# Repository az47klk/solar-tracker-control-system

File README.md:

# Solar-Tracker: Güneş Paneli Güç Takip ve Kontrol Sistemi

Bu proje, hareketli güneş paneli sistemlerinin güvenli şekilde çalışmaları için, anlık güç takibi yapmak ve çevresel verileri (sıcaklık, zaman vb.) yönetmek amacıyla geliştirilmiş bir gömülü kontrol sistemidir. Proje; donanım tasarımı (PCB), düşük seviyeli sürücü yazılımı ve endüstriyel haberleşme protokollerini kapsamaktadır.

## Teknik Özellikler
Sistem, endüstriyel standart gereksinimleri dikkate alınarak tasarlanmıştır:

* **Kontrol Birimi:** STM32 Mikrodenetleyici tabanlı mimari 
* **Haberleşme:** * **RS485 (Modbus):** Uzak mesafe veri iletimi ve endüstriyel cihaz entegrasyonu.
    * **I2C & UART:** Sensör ve çevre birimleri ile iletişim.
* **Donanım Bileşenleri:**
    * **MAX485:** Diferansiyel sinyal işleme ve gürültü bağışıklığı.
    * **DS1307 RTC:** Gerçek zamanlı saat takibi ile zaman bazlı hareket senaryoları.
    * **JW2 Röle Kontrolü:** Panel hareket mekanizması için güç yönetimi.
    * **128x64 OLED:** Yerel kullanıcı arayüzü ve anlık veri izleme.
* **PCB Tasarımı:** **KiCad** kullanılarak hazırlanan, sinyal bütünlüğü ve güç dağıtımı optimize edilmiş özgün devre kartı.

## Donanım Mimarisi
Proje kapsamında geliştirilen güç takip kartı şu işlevleri yerine getirmektedir:
1.  **Veri Toplama:** Sıcaklık sensörlerinden gelen verilerin işlenmesi.
2.  **Güç Yönetimi:** Röle katmanı üzerinden motor sürücülerin kontrol edilmesi.
3.  **HMI Entegrasyonu:** Sistem durumunun (gerilim, akım, zaman, sıcaklık) OLED ekran üzerinde gösterilmesi.
4.  **Haberleşme Katmanı:** Toplanan verilerin RS485 üzerinden merkezi bir birime aktarılması.

## Dosya Yapısı
* `/Hardware`: KiCad şema ve PCB tasarım dosyaları (Gerber dahil).
* `/Software`: C++ ile geliştirilen kontrol yazılımı ve sürücü kütüphaneleri.

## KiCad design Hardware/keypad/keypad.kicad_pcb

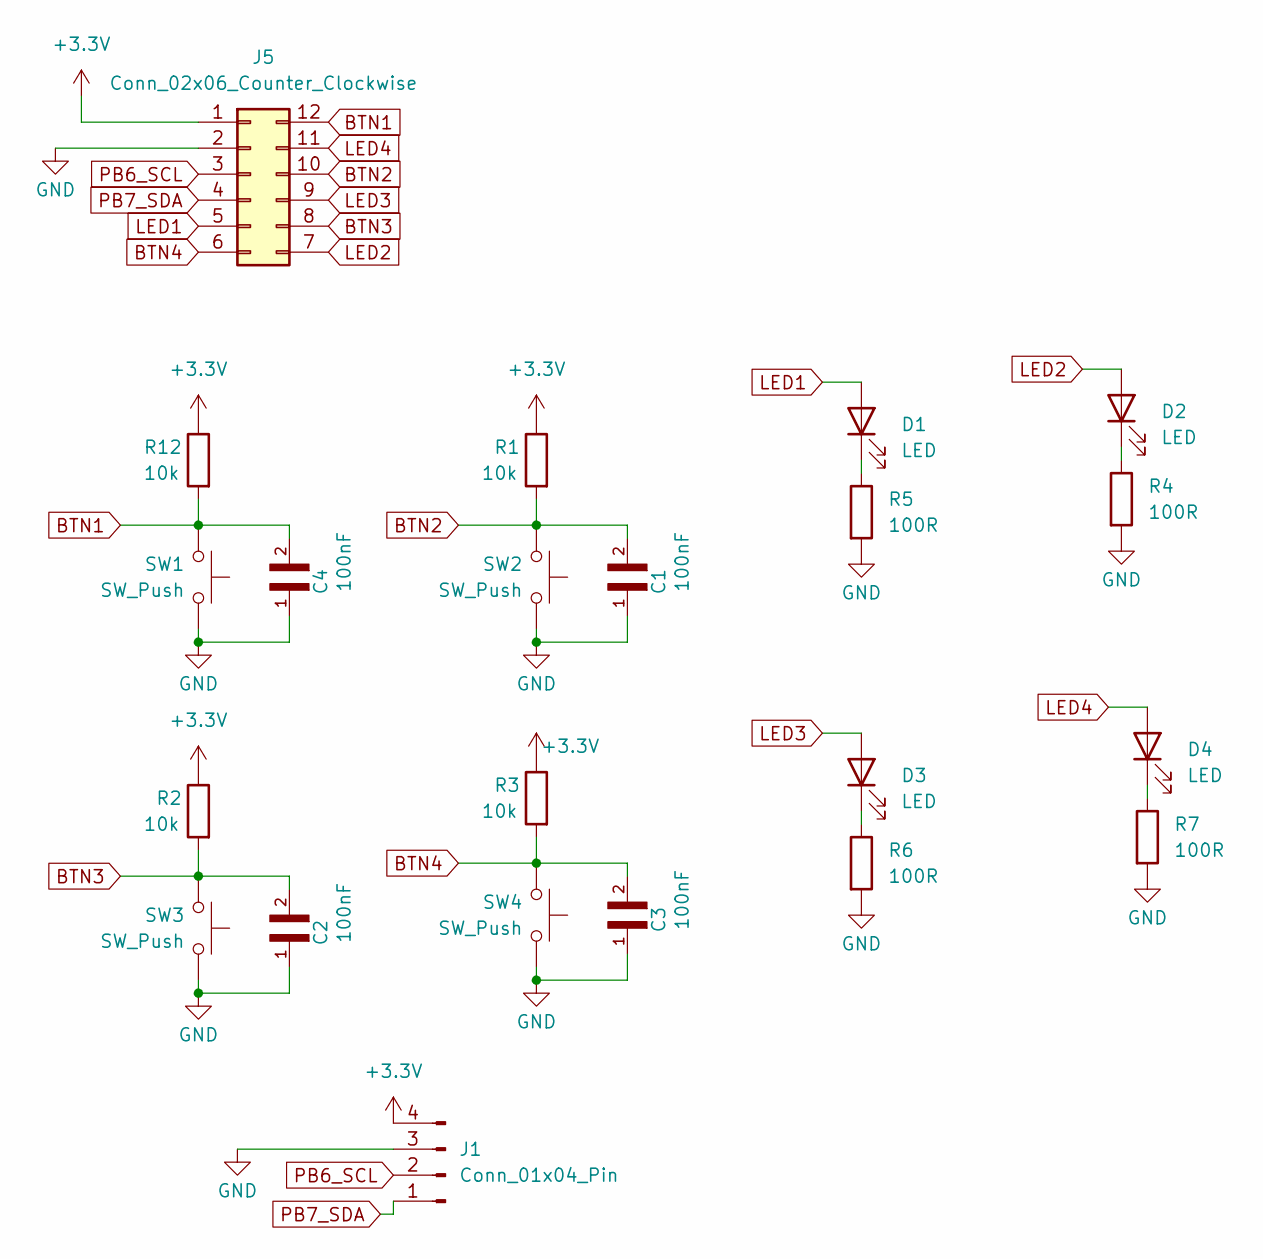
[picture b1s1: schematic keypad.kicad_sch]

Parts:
C1, C2, C3, C4: 100nF; C_0402_1005Metric
D1, D2, D3, D4: LED; LED_0805_2012Metric
J1: Conn_01x04_Pin; PinHeader_1x04_P2.54mm_Vertical
J5: Conn_02x06_Counter_Clockwise; IDC-Header_2x06_P2.54mm_Vertical
R1, R2, R3, R12: 10k; R_0603_1608Metric
R4, R5, R6, R7: 100R; R_0603_1608Metric
SW1, SW2, SW3, SW4: SW_Push; SW_PUSH_6mm

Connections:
+3.3V: J1.4, J5.1, R1.1, R2.1, R3.1, R12.1
BTN1: C4.2, J5.12, R12.2, SW1.2
BTN2: C1.2, J5.10, R1.2, SW2.2
BTN3: C2.2, J5.8, R2.2, SW3.2
BTN4: C3.2, J5.6, R3.2, SW4.2
GND: C1.1, C2.1, C3.1, C4.1, J1.3, J5.2, R4.2, R5.2, R6.2, R7.2, SW1.1, SW2.1, SW3.1, SW4.1
LED1: D1.2 (A), J5.5
LED2: D2.2 (A), J5.7
LED3: D3.2 (A), J5.9
LED4: D4.2 (A), J5.11
unnamed: D1.1 (K), R5.1
unnamed: D2.1 (K), R4.1
unnamed: D3.1 (K), R6.1
unnamed: D4.1 (K), R7.1
PB6_SCL: J1.2, J5.3
PB7_SDA: J1.1, J5.4

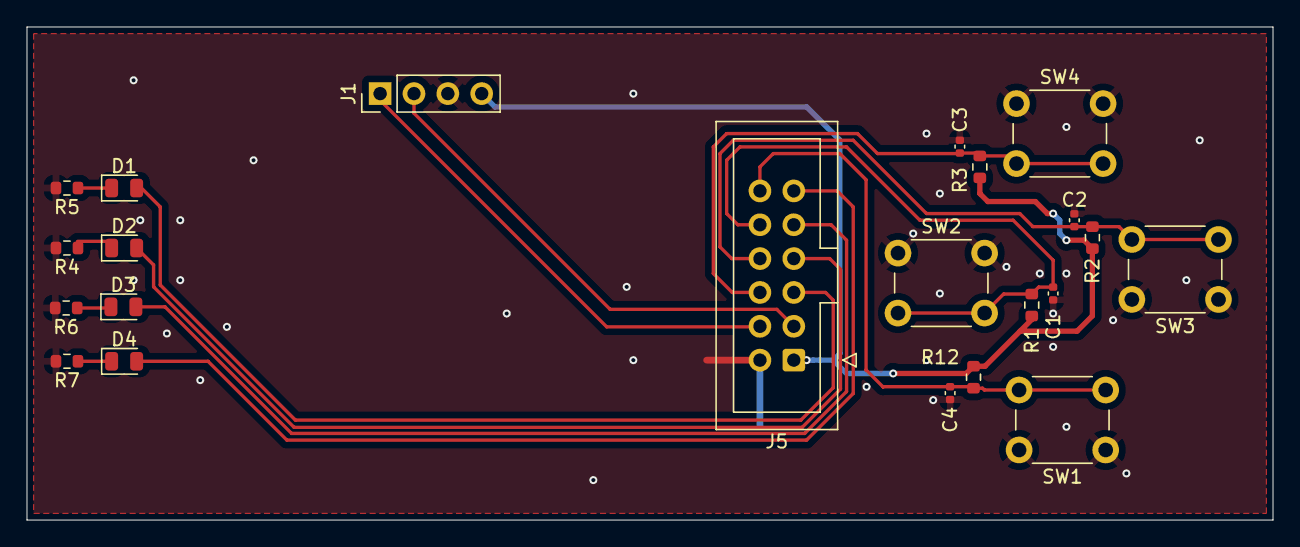
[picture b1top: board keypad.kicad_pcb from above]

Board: 2 copper layers, 93.5 x 37.0 mm, 22 parts (0 on the bottom side), 16 nets.

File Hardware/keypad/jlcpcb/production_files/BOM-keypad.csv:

Comment,Designator,Footprint,LCSC,Quantity
100R,"R4,R5,R6,R7",R_0603_1608Metric,C22775,4
100nF,"C1,C2,C3,C4",C_0402_1005Metric,C1525,4
10k,"R1,R12,R2,R3",R_0603_1608Metric,C15401,4
Conn_01x04_Pin,J1,PinHeader_1x04_P2.54mm_Vertical,C5116530,1
Conn_02x06_Counter_Clockwise,J5,IDC-Header_2x06_P2.54mm_Vertical,C5224012,1
LED,"D1,D2,D3,D4",LED_0805_2012Metric,C2296,4
SW_Push,SW4,SW_PUSH_6mm,,1
SW_Push,SW2,SW_PUSH_6mm,,1
SW_Push,SW3,SW_PUSH_6mm,,1
SW_Push,SW1,SW_PUSH_6mm,,1

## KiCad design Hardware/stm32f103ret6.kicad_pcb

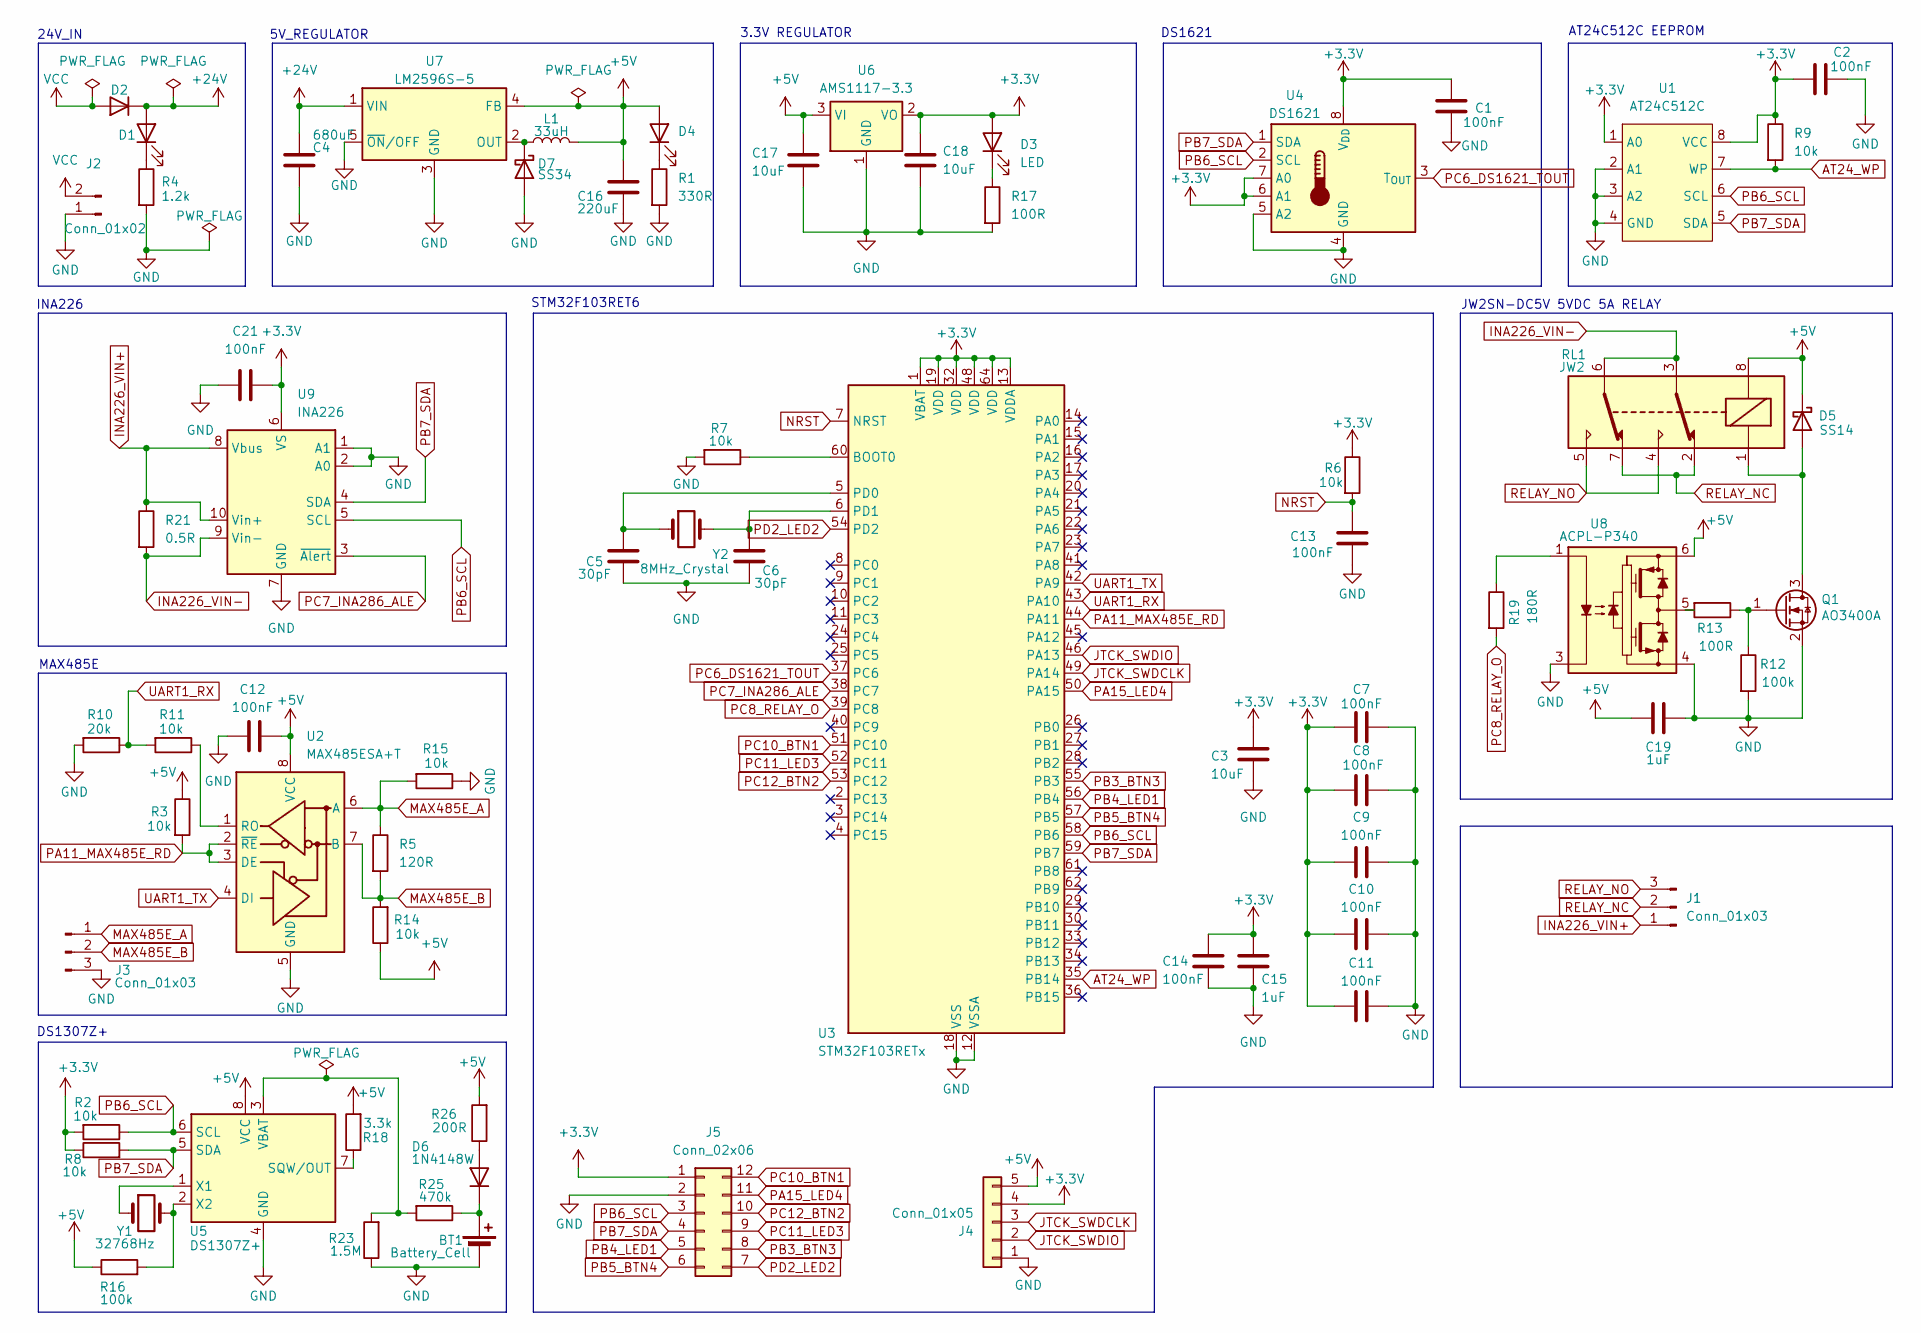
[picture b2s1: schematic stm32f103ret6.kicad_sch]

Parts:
BT1: Battery_Cell; CR2032_battery
C1, C7, C8, C9, C10, C11, C13, C14: 100nF; C_0603_1608Metric
C2, C12, C21: 100nF; C_0402_1005Metric
C3, C17, C18: 10uF; CP_EIA-3216-18_Kemet-A
C4: 680uF; CP_Elec_12.5x13.5
C5, C6: 30pF; C_0603_1608Metric
C15, C19: 1uF; C_0603_1608Metric
C16: 220uF; CP_Elec_6.3x7.7
D1, D3, D4: LED; LED_0805_2012Metric
D2: D; D_SMB
D5: SS14; D_SMA
D6: 1N4148W; D_SOD-123
D7: SS34; D_SMA
J1, J3: Conn_01x03; PhoenixContact_MSTBA_2,5_3-G-5,08_1x03_P5.08mm_Horizontal
J2: Conn_01x02; PhoenixContact_MSTBA_2,5_2-G-5,08_1x02_P5.08mm_Horizontal
J4: Conn_01x05; PinHeader_1x05_P2.54mm_Vertical
J5: Conn_02x06; IDC-Header_2x06_P2.54mm_Vertical
L1: 33uH; L_Wuerth_HCM-1052
Q1: AO3400A; SOT-23
R1: 330R; R_0603_1608Metric
R2, R6, R8, R9: 10k; R_0603_1608Metric
R3, R7, R11, R14, R15: 10k; R_0402_1005Metric
R4: 1.2k; R_0603_1608Metric
R5: 120R; R_0603_1608Metric_Pad0.98x0.95mm_HandSolder
R10: 20k; R_0402_1005Metric
R12, R16: 100k; R_0603_1608Metric
R13, R17: 100R; R_0603_1608Metric
R18: 3.3k; R_0402_1005Metric
R19: 180R; R_0603_1608Metric
R21: 0.5R; R_2512_6332Metric
R23: 1.5M; R_0603_1608Metric
R25: 470k; R_0603_1608Metric
R26: 200R; R_0603_1608Metric
RL1: JW2; Relay_DPDT_Panasonic_JW2
U1: AT24C512C; SOP-8_3.76x4.96mm_P1.27mm
U2: MAX485ESA+T; SOIC-8_3.9x4.9mm_P1.27mm
U3: STM32F103RETx; LQFP-64_10x10mm_P0.5mm
U4: DS1621; SOIC-8_3.9x4.9mm_P1.27mm
U5: DS1307Z+; SOIC-8_3.9x4.9mm_P1.27mm
U6: AMS1117-3.3; SOT-223-3_TabPin2
U7: LM2596S-5; TO-263-5_TabPin3
U8: ACPL-P340; SO-6L_10x3.84mm_P1.27mm
U9: INA226; VSSOP-10_3x3mm_P0.5mm
Y1: 32768Hz; Crystal_SMD_3215-2Pin_3.2x1.5mm
Y2: 8MHz_Crystal; Crystal_SMD_5032-2Pin_5.0x3.2mm

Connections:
+3.3V: C1.2, C2.1, C3.1, C7.2, C8.2, C9.2, C10.2, C11.2, C14.1, C15.1, C18.1, C21.2, D3.2 (A), J4.4, J5.1, R2.2, R6.1, R8.1, R9.1, U1.1 (A0), U1.8 (VCC), U3.1 (VBAT), U3.13 (VDDA), U3.19 (VDD), U3.32 (VDD), U3.48 (VDD), U3.64 (VDD), U4.6 (A1), U4.7 (A0), U4.8 (V_{DD}), U6.2 (VO), U9.6 (VS)
+5V: C12.2, C16.1, C17.1, C19.2, D4.2 (A), D5.1 (K), J4.5, L1.2, R3.1, R14.1, R16.1, R18.2, R26.2, RL1.8, U2.8 (VCC), U5.8 (VCC), U6.3 (VI), U7.4 (FB), U8.6 (VCC)
+24V: C4.1, D1.2 (A), D2.1 (K), U7.1 (VIN)
AT24_WP: R9.2, U1.7 (WP), U3.35 (PB14)
GND: BT1.2 (-), C1.1, C2.2, C3.2, C4.2, C5.2, C6.2, C7.1, C8.1, C9.1, C10.1, C11.1, C12.1, C13.2, C14.2, C15.2, C16.2, C17.2, C18.2, C19.1, C21.1, D7.2 (A), J2.1, J3.3, J4.1, J5.2, Q1.2 (S), R1.2, R4.2, R7.2, R10.2, R12.2, R15.1, R17.2, R23.1, U1.2 (A1), U1.3 (A2), U1.4 (GND), U2.5 (GND), U3.12 (VSSA), U3.18 (VSS), U3.31 (VSS), U3.47 (VSS), U3.63 (VSS), U4.4 (GND), U4.5 (A2), U5.4 (GND), U6.1 (GND), U7.3 (GND), U7.5 (~ON/OFF), U8.3 (C), U8.4 (VEE), U9.1 (A1), U9.2 (A0), U9.7 (GND)
INA226_VIN+: J1.1, R21.1, U9.8 (Vbus), U9.10 (Vin+)
INA226_VIN-: R21.2, RL1.3, RL1.6, U9.9 (Vin-)
JTCK_SWDCLK: J4.3, U3.49 (PA14)
JTCK_SWDIO: J4.2, U3.46 (PA13)
MAX485E_A: J3.1, R5.1, R15.2, U2.6 (A)
MAX485E_B: J3.2, R5.2, R14.2, U2.7 (B)
NRST: C13.1, R6.2, U3.7 (NRST)
unnamed: BT1.1 (+), D6.1 (K), R25.1
unnamed: D1.1 (K), R4.1
unnamed: D3.1 (K), R17.1
unnamed: D4.1 (K), R1.1
unnamed: D5.2 (A), Q1.3 (D), RL1.1
unnamed: D6.2 (A), R26.1
unnamed: D7.1 (K), L1.1, U7.2 (OUT)
unnamed: Q1.1 (G), R12.1, R13.1
unnamed: R11.1, U2.1 (RO)
unnamed: R7.1, U3.60 (BOOT0)
unnamed: C5.1, U3.5 (PD0), Y2.1
unnamed: C6.1, U3.6 (PD1), Y2.2
unnamed: R18.1, U5.7 (SQW/OUT)
unnamed: R23.2, R25.2, U5.3 (VBAT)
unnamed: U5.1 (X1), Y1.1
unnamed: R16.2, U5.2 (X2), Y1.2
unnamed: R19.1, U8.1 (A)
unnamed: R13.2, U8.5 (VO)
PA11_MAX485E_RD: R3.2, U2.2 (~RE), U2.3 (DE), U3.44 (PA11)
PA15_LED4: J5.11, U3.50 (PA15)
PB3_BTN3: J5.8, U3.55 (PB3)
PB4_LED1: J5.5, U3.56 (PB4)
PB5_BTN4: J5.6, U3.57 (PB5)
PB6_SCL: J5.3, R2.1, U1.6 (SCL), U3.58 (PB6), U4.2 (SCL), U5.6 (SCL), U9.5 (SCL)
PB7_SDA: J5.4, R8.2, U1.5 (SDA), U3.59 (PB7), U4.1 (SDA), U5.5 (SDA), U9.4 (SDA)
PC6_DS1621_TOUT: U3.37 (PC6), U4.3 (T_{OUT})
PC7_INA286_ALE: U3.38 (PC7), U9.3 (~Alert)
PC8_RELAY_O: R19.2, U3.39 (PC8)
PC10_BTN1: J5.12, U3.51 (PC10)
PC11_LED3: J5.9, U3.52 (PC11)
PC12_BTN2: J5.10, U3.53 (PC12)
PD2_LED2: J5.7, U3.54 (PD2)
RELAY_NC: J1.2, RL1.2, RL1.7
RELAY_NO: J1.3, RL1.4, RL1.5
UART1_RX: R10.1, R11.2, U3.43 (PA10)
UART1_TX: U2.4 (DI), U3.42 (PA9)
VCC: D2.2 (A), J2.2

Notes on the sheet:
STM32F103RET6
MAX485E
JW2SN-DC5V 5VDC 5A RELAY
3.3V REGULATOR
5V_REGULATOR
24V_IN
AT24C512C EEPROM
DS1621
DS1307Z+
INA226

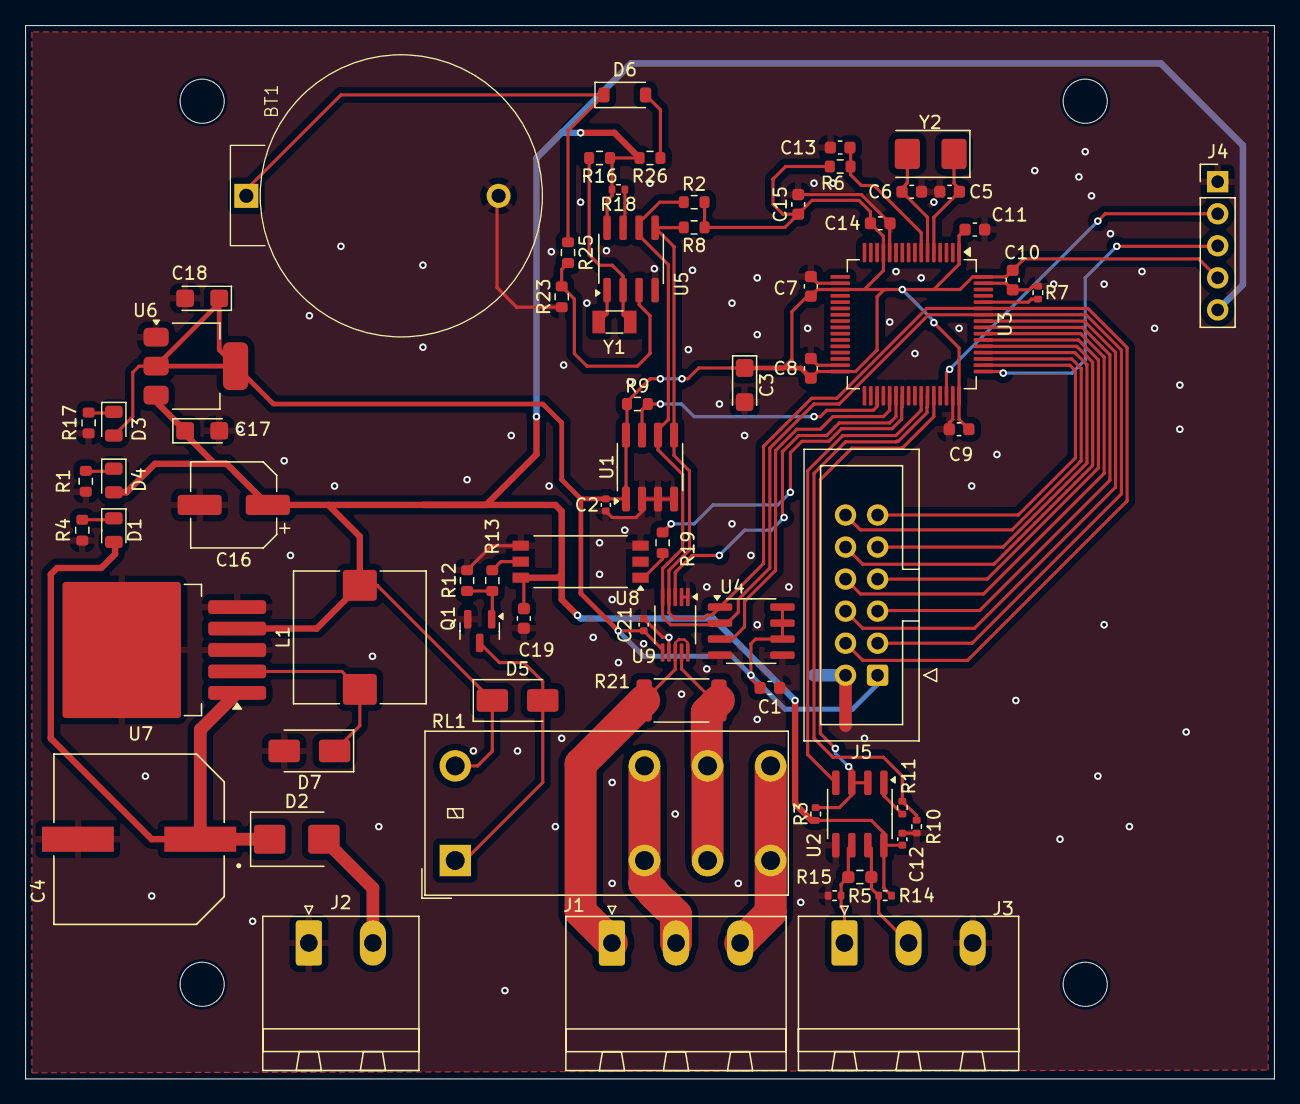
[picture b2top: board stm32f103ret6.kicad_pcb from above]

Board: 2 copper layers, 99.0 x 83.5 mm, 70 parts (0 on the bottom side), 49 nets.

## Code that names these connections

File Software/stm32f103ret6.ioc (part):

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Mcu.Name=STM32F103R(C-D-E)Tx
Mcu.Package=LQFP64
Mcu.UserName=STM32F103RETx
PA10.Mode=Asynchronous
PA10.Signal=USART1_RX
PA11.Signal=GPIO_Output
PA13.Mode=Serial_Wire
PA13.Signal=SYS_JTMS-SWDIO
PA14.Mode=Serial_Wire
PA14.Signal=SYS_JTCK-SWCLK
PA9.Mode=Asynchronous
PA9.Signal=USART1_TX
PB14.Signal=GPIO_Output
PB3.Signal=GPIO_Input
PB4.Signal=GPIO_Output
PB5.Signal=GPIO_Input
PB6.Mode=I2C
PB6.Signal=I2C1_SCL
PB7.Mode=I2C
PB7.Signal=I2C1_SDA
PC10.Signal=GPIO_Input
PC11.Signal=GPIO_Output
PC12.Signal=GPIO_Input
PC6.Signal=GPIO_Output
PC7.Signal=GPIO_Input
PC8.Signal=GPIO_Input
PD0-OSC_IN.Mode=HSE-External-Oscillator
PD0-OSC_IN.Signal=RCC_OSC_IN
PD1-OSC_OUT.Mode=HSE-External-Oscillator
PD1-OSC_OUT.Signal=RCC_OSC_OUT
PD2.Signal=GPIO_Output
board=custom

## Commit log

2026-03-02 Upload files
